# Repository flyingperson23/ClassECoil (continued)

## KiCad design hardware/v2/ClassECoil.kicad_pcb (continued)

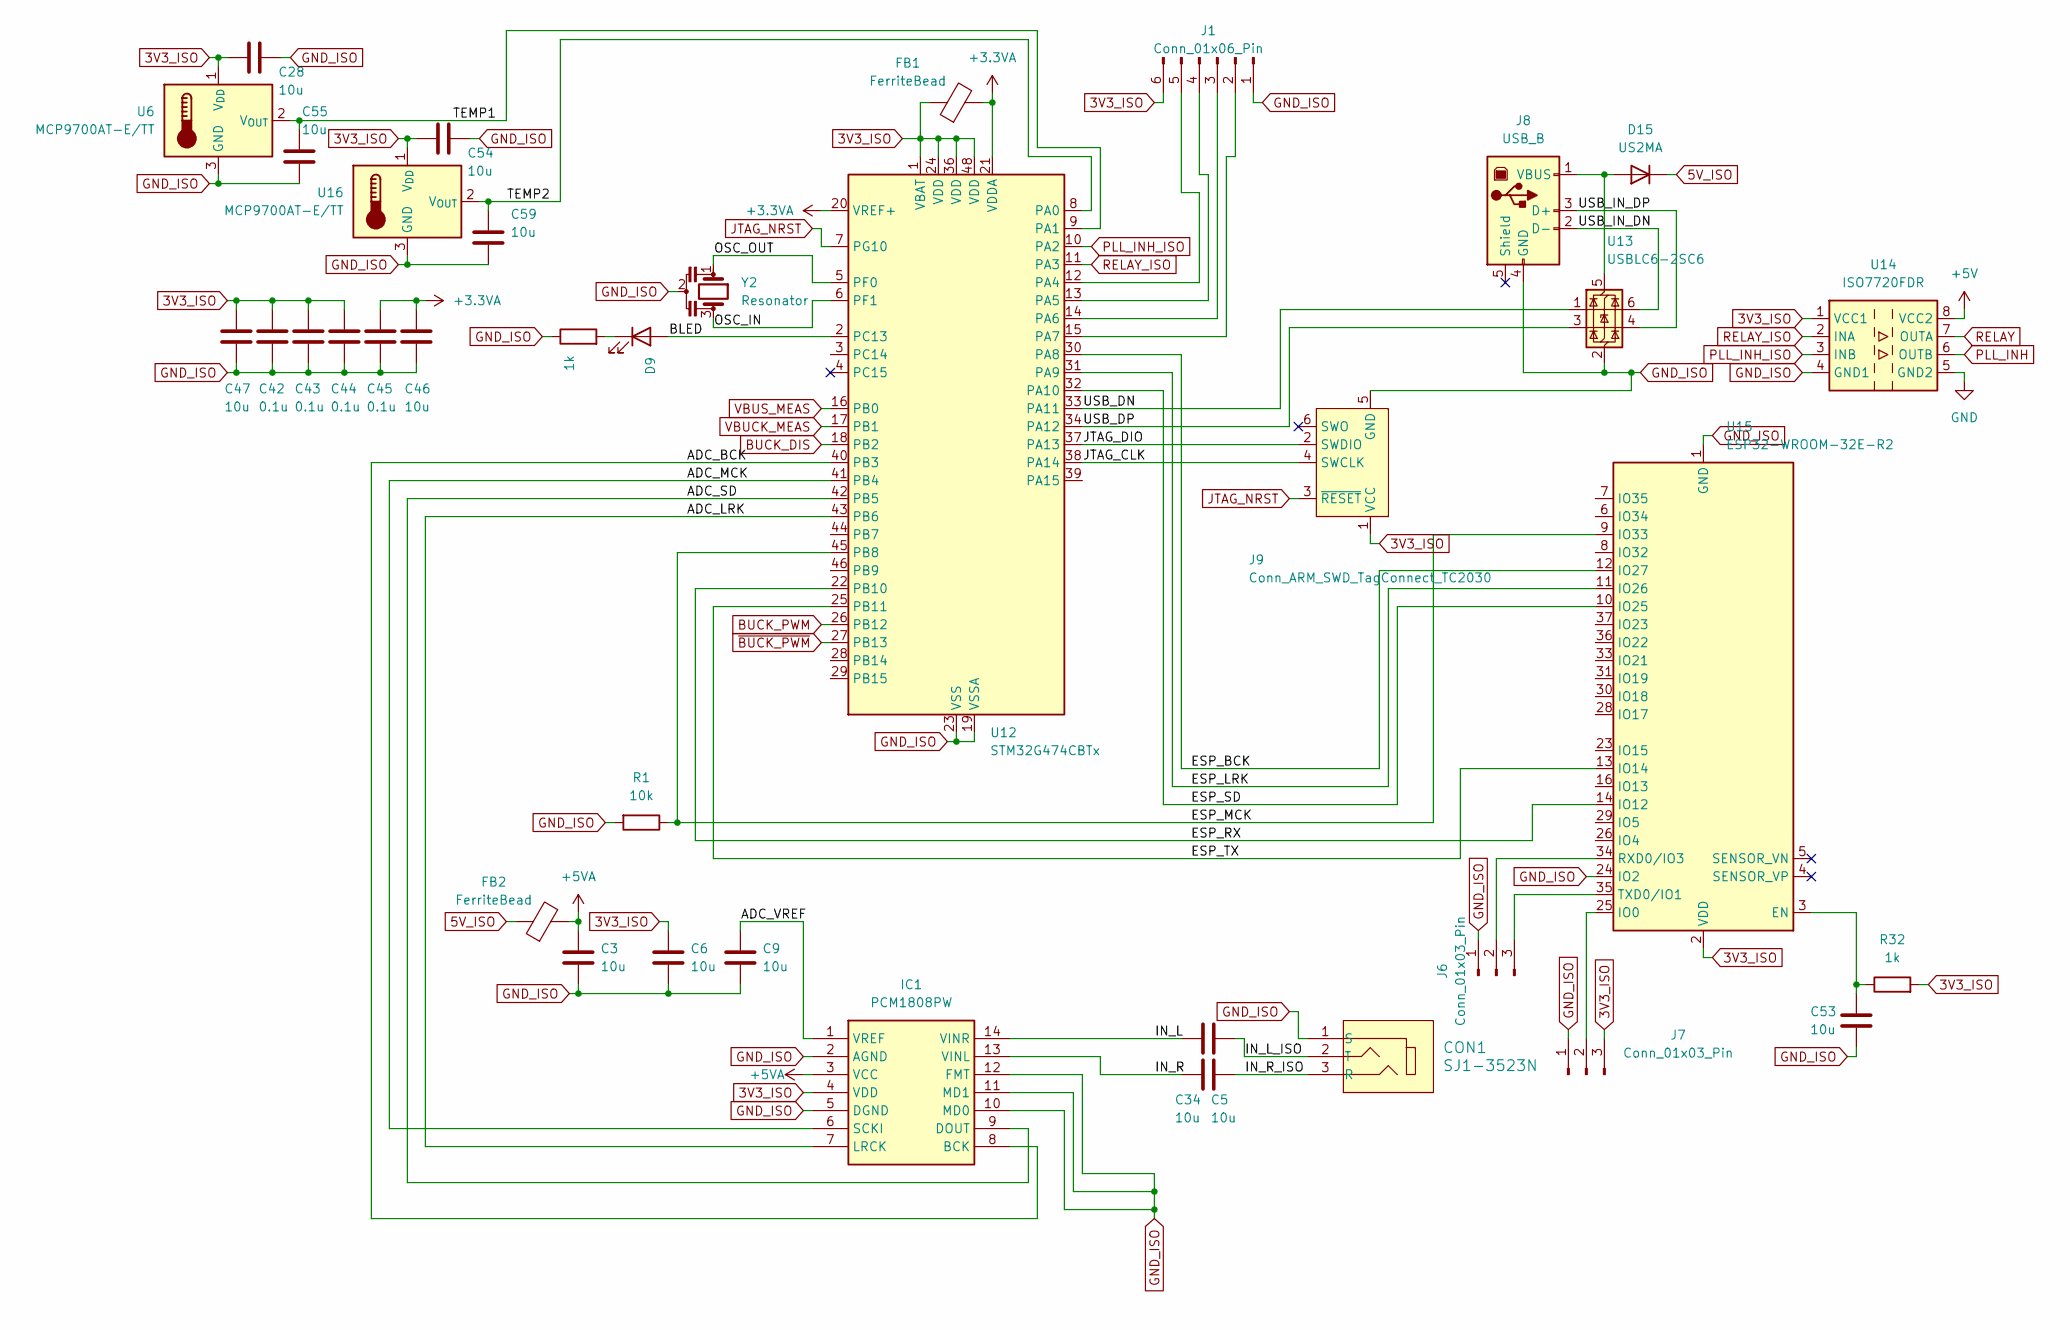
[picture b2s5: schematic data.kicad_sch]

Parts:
C3, C5, C6, C9, C28, C34, C46, C47, C53, C54, C55, C59: 10u; C_0805_2012Metric
C42, C43, C44, C45: 0.1u; C_0805_2012Metric
CON1: SJ1-3523N; Headphone_Jack_3.5mm_SJ1-3523N; MPN SJ1-3523N; Digi-Key_PN CP1-3523N-ND
D9: LED; LED_0805_2012Metric
D15: US2MA; D_SMA
FB1, FB2: FerriteBead; L_0805_2012Metric
IC1: PCM1808PW; TSSOP-14_4.4x5mm_P0.65mm; Mouser Part Number 595-PCM1808PW
J1: Conn_01x06_Pin; Molex_KK-254_AE-6410-06A_1x06_P2.54mm_Vertical
J6, J7: Conn_01x03_Pin; PinHeader_1x03_P2.54mm_Vertical
J8: USB_B; USB_B_OST_USB-B1HSxx_Horizontal
J9: Conn_ARM_SWD_TagConnect_TC2030; Tag-Connect_TC2030-IDC-FP_2x03_P1.27mm_Vertical
R1: 10k; R_0805_2012Metric
R10, R32: 1k; R_0805_2012Metric
U6, U16: MCP9700AT-E/TT; SOT-23
U12: STM32G474CBTx; LQFP-48_7x7mm_P0.5mm
U13: USBLC6-2SC6; SOT-23-6
U14: ISO7720FDR; SOIC-8_3.9x4.9mm_P1.27mm
U15: ESP32-WROOM-32E-R2; ESP32-WROOM-32D
Y2: Resonator; Resonator_SMD_Murata_CSTxExxV-3Pin_3.0x1.1mm

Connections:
3V3_ISO: C6.2, C28.2, C42.1, C43.1, C44.1, C47.2, C54.2, FB1.1, IC1.4 (VDD), J1.6, J7.3, J9.1 (VCC), R32.2, U6.1 (V_{DD}), U12.1 (VBAT), U12.24 (VDD), U12.36 (VDD), U12.48 (VDD), U14.1 (VCC1), U15.2 (VDD), U16.1 (V_{DD}); also elsewhere on the board
5V_ISO: D15.1 (K), FB2.1; also elsewhere on the board
+3.3VA: C45.1, C46.2, FB1.2, U12.20 (VREF+), U12.21 (VDDA)
+5V: U14.8 (VCC2); also elsewhere on the board
+5VA: C3.2, FB2.2, IC1.3 (VCC)
/Data Processing/ADC_BCK: IC1.8 (BCK), U12.40 (PB3)
/Data Processing/ADC_LRK: IC1.7 (LRCK), U12.43 (PB6)
/Data Processing/ADC_MCK: IC1.6 (SCKI), U12.41 (PB4)
/Data Processing/ADC_SD: IC1.9 (DOUT), U12.42 (PB5)
/Data Processing/ADC_VREF: C9.2, IC1.1 (VREF)
/Data Processing/BLED: D9.2 (A), U12.2 (PC13)
/Data Processing/ESP_BCK: U12.30 (PA8), U15.12 (IO27)
/Data Processing/ESP_LRK: U12.31 (PA9), U15.11 (IO26)
/Data Processing/ESP_MCK: R1.1, U12.45 (PB8), U15.9 (IO33)
/Data Processing/ESP_RX: U12.22 (PB10), U15.14 (IO12)
/Data Processing/ESP_SD: U12.32 (PA10), U15.10 (IO25)
/Data Processing/ESP_TX: U12.25 (PB11), U15.13 (IO14)
/Data Processing/IN_L: C5.1, IC1.14 (VINR)
/Data Processing/IN_L_ISO: C5.2, CON1.2 (T)
/Data Processing/IN_R: C34.1, IC1.13 (VINL)
/Data Processing/IN_R_ISO: C34.2, CON1.3 (R)
/Data Processing/JTAG_CLK: J9.4 (SWCLK), U12.38 (PA14)
/Data Processing/JTAG_DIO: J9.2 (SWDIO), U12.37 (PA13)
/Data Processing/OSC_IN: U12.6 (PF1), Y2.3
/Data Processing/OSC_OUT: U12.5 (PF0), Y2.1
/Data Processing/TEMP1: C55.1, U6.2 (V_{OUT}), U12.9 (PA1)
/Data Processing/TEMP2: C59.1, U12.8 (PA0), U16.2 (V_{OUT})
/Data Processing/USB_DN: U12.33 (PA11), U13.1 (I/O1)
/Data Processing/USB_DP: U12.34 (PA12), U13.3 (I/O2)
/Data Processing/USB_IN_DN: J8.2 (D-), U13.6 (I/O1)
/Data Processing/USB_IN_DP: J8.3 (D+), U13.4 (I/O2)
BUCK_DIS: U12.18 (PB2); also elsewhere on the board
BUCK_PWM: U12.26 (PB12); also elsewhere on the board
GND: U14.5 (GND2); also elsewhere on the board
GND_ISO: C3.1, C6.1, C9.1, C28.1, C42.2, C43.2, C44.2, C45.2, C46.1, C47.1, C53.1, C54.1, C55.2, C59.2, CON1.1 (S), IC1.2 (AGND), IC1.5 (DGND), IC1.10 (MD0), IC1.11 (MD1), IC1.12 (FMT), J1.1, J6.1, J7.1, J8.4 (GND), J9.5 (GND), R1.2, R10.1, U6.3 (GND), U12.19 (VSSA), U12.23 (VSS), U12.35 (VSS), U12.47 (VSS), U13.2 (GND), U14.4 (GND1), U15.1 (GND), U15.15 (GND), U15.24 (IO2), U15.38 (GND), U15.39 (GND), U16.3 (GND), Y2.2; also elsewhere on the board
JTAG_NRST: J9.3 (~RESET), U12.7 (PG10)
unnamed: D9.1 (K), R10.2
unnamed: D15.2 (A), J8.1 (VBUS), U13.5 (VBUS)
unnamed: J1.2, U12.15 (PA7)
unnamed: J1.3, U12.14 (PA6)
unnamed: J1.4, U12.13 (PA5)
unnamed: J1.5, U12.12 (PA4)
unnamed: J6.2, U15.34 (RXD0/IO3)
unnamed: J6.3, U15.35 (TXD0/IO1)
unnamed: J7.2, U15.25 (IO0)
unnamed: C53.2, R32.1, U15.3 (EN)
PLL_INH: U14.6 (OUTB); also elsewhere on the board
PLL_INH_ISO: U12.10 (PA2), U14.3 (INB)
RELAY: U14.7 (OUTA); also elsewhere on the board
RELAY_ISO: U12.11 (PA3), U14.2 (INA)
VBUCK_MEAS: U12.17 (PB1); also elsewhere on the board
VBUS_MEAS: U12.16 (PB0); also elsewhere on the board
~BUCK_PWM: U12.27 (PB13); also elsewhere on the board

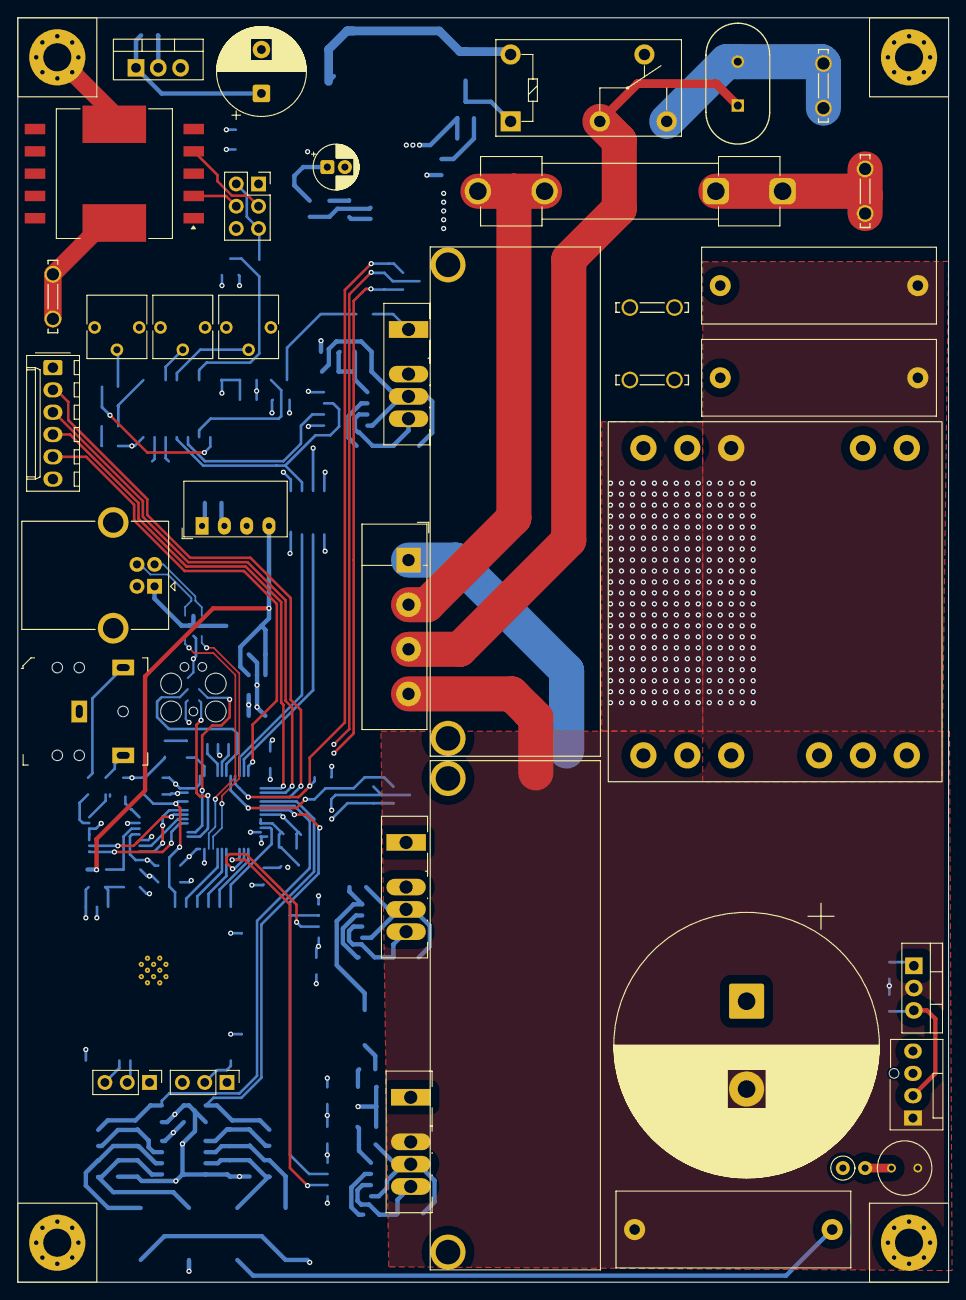
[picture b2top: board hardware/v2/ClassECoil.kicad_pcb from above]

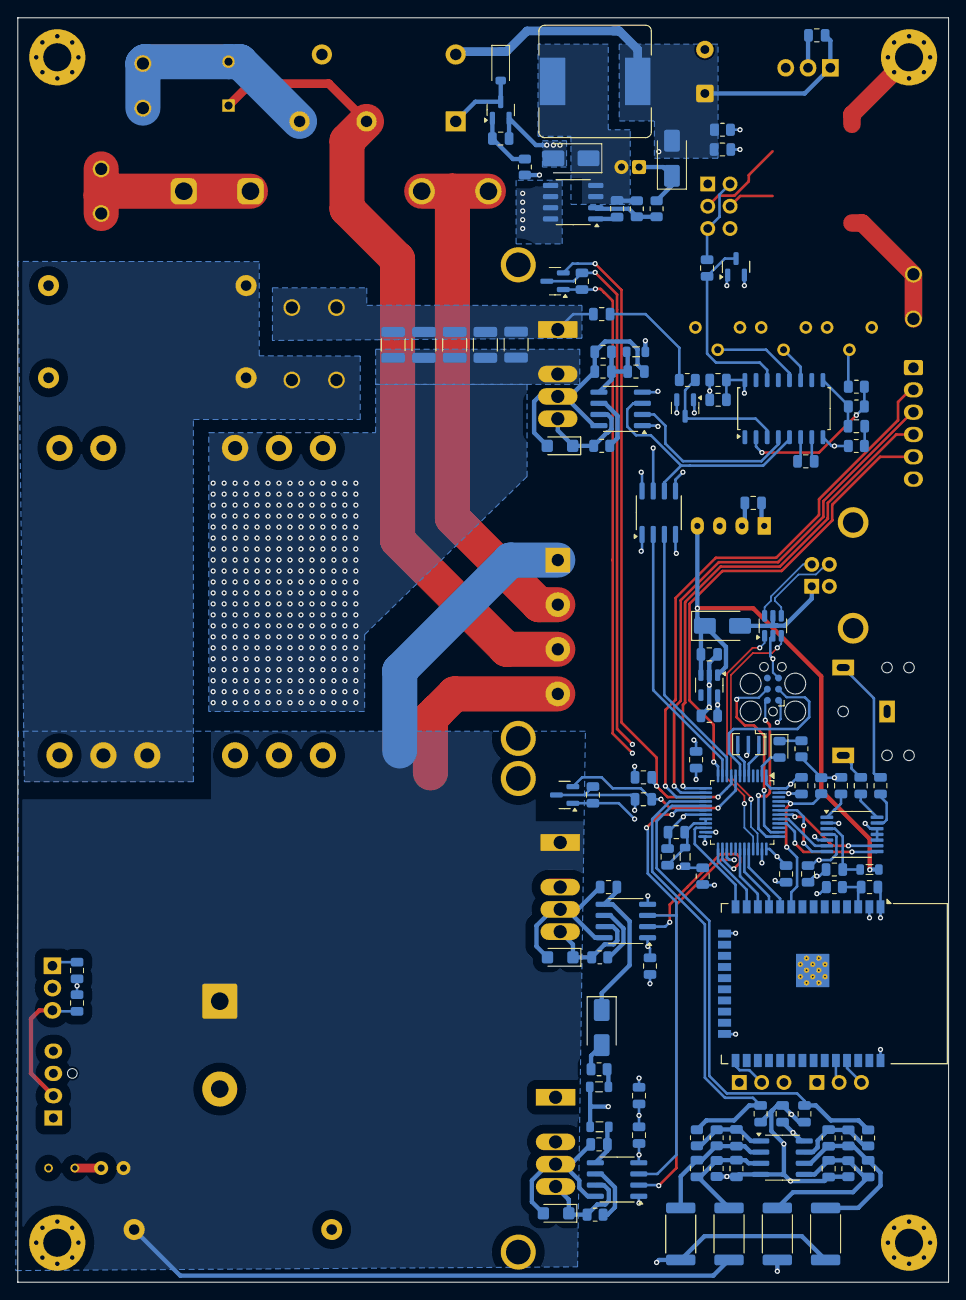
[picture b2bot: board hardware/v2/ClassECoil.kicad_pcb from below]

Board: 4 copper layers, 106.0 x 144.0 mm, 153 parts (112 on the bottom side), 107 nets.

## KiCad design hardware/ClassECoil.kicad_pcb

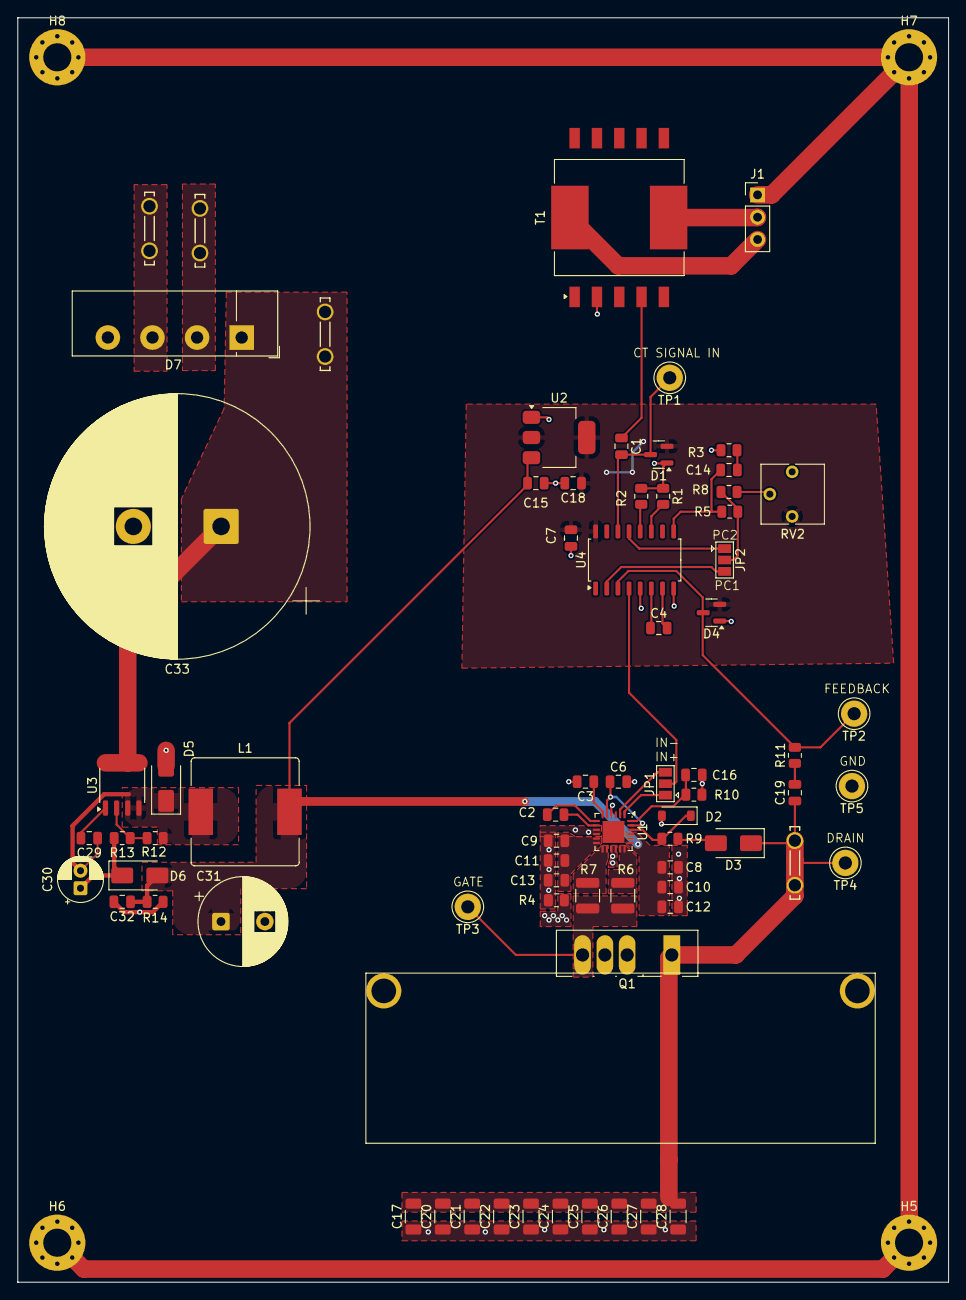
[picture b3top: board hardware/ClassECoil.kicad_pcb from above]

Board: 2 copper layers, 106.0 x 144.0 mm, 78 parts (0 on the bottom side), 43 nets.

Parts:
C1: 10n; C_0805_2012Metric
C2: 470n; C_0805_2012Metric
C3, C6, C7, C8, C9, C10, C11, C15, C18: 2.2u; C_0805_2012Metric
C4: 100p; C_0805_2012Metric
C12, C13, C16: 100n; C_0805_2012Metric
C14, C19: 1n; C_0805_2012Metric
C17, C20, C21, C22, C23, C24, C25, C26, C27, C28: 300p; C_1206_3216Metric
C29, C32: 0.1u; C_0805_2012Metric
C30: 860010572002; CP_Radial_D5.0mm_P2.00mm
C31: 860240475009; CP_Radial_D10.0mm_P5.00mm
C33: 861141085015; CP_Radial_D30.0mm_P10.00mm_SnapIn
D1, D4: BAV99; SOT-23
D2: MBR0540; D_SOD-123
D3: US1M; D_SMA
D5, D6: US2MA; D_SMA
D7: KBU8J; Diode_Bridge_Vishay_KBU
H5, H6, H7, H8: MountingHole_Pad; MountingHole_3.2mm_M3_Pad_Via
HS1: Heatsink_Pad; C40_Half
J1: Conn_01x03_Pin; PinHeader_1x03_P2.54mm_Vertical
J2, J3, J4, J5: Conn_01x01; SPADE_726386-2
JP1, JP2: SolderJumper_3_Open; SolderJumper-3_P1.3mm_Open_Pad1.0x1.5mm
L1: SRR1210A-821M; L_Bourns_SRR1210A
Q1: C3M0030090K; TO-247-4_Vertical
R1: 8.2k; R_0805_2012Metric
R2: 12k; R_0805_2012Metric
R3: 100R; R_0805_2012Metric
R4: 0R; R_0805_2012Metric
R5, R8: 60k; R_0805_2012Metric
R6, R7: 10R; R_1210_3225Metric
R9: 5.1k; R_0805_2012Metric
R10: 100k; R_0805_2012Metric
R11: 330k; R_0805_2012Metric
R12, R14: 10k; R_0805_2012Metric
R13: 62k; R_0805_2012Metric
RV2: T73YP103KT20; Potentiometer_Vishay_T73YP_Vertical
T1: CST2010-030LD; Transformer_Coilcraft_CST2010
TP1, TP2, TP3, TP4, TP5: TestPoint; Pin_D1.3mm_L11.0mm_LooseFit
U1: NCV51705MNTWG; QFN-24-1EP_4x4mm_P0.5mm_EP2.5x2.5mm
U2: NCP1117-5.0_SOT223; SOT-223-3_TabPin2
U3: AP3928S-13; SO-8_3.9x4.9mm_P1.27mm
U4: CD74HCT4046AM1; SOIC-16_4.55x10.3mm_P1.27mm

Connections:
+5V: C7.1, C18.1, D1.2 (A), D4.2 (A), RV2.3, U2.2 (VO), U4.16 (VDD)
BUCK_FB: R12.1, R13.1, U3.2 (FB)
Earth: H5.1, H6.1, H7.1, H8.1, J1.1
FEEDBACK: D4.3 (K), R11.2, TP2.1, U4.3 (RefIn)
GND: C3.2, C6.2, C7.2, C15.2, C16.1, C17.1, C18.2, C20.1, C21.1, C22.1, C23.1, C24.1, C25.1, C26.1, C27.1, C28.1, C31.2, C32.2, C33.2, D1.1 (K), D4.1 (K), D5.2 (A), D7.4 (-), Q1.2 (S), R1.1, R2.1, R3.2, R4.1, R10.1, R14.2, RV2.1, T1.2, TP5.1, U1.4 (SGND), U2.1 (GND), U4.5 (Inh), U4.8 (VSS)
unnamed: C1.1, T1.4
unnamed: C14.2, R3.1
unnamed: C19.2, R11.1
unnamed: D2.1 (K), R9.2, U1.22 (DESAT)
unnamed: D3.2 (A), R9.1
unnamed: C17.2, C19.1, C20.2, C21.2, C22.2, C23.2, C24.2, C25.2, C26.2, C27.2, C28.2, D3.1 (K), J3.1, Q1.1 (D), TP4.1
unnamed: C29.1, C30.2, D5.1 (K), L1.1, R12.2, U3.3 (GNDA), U3.4 (GNDP)
unnamed: C30.1, D6.1 (K), R13.2
unnamed: J1.2, T1.12
unnamed: J1.3, T1.11
unnamed: D7.3, J4.1
unnamed: D7.2, J5.1
unnamed: JP1.1 (A), U1.1 (IN+)
unnamed: JP1.3 (B), U1.2 (IN-)
unnamed: JP1.2 (C), U4.4 (FOUT)
unnamed: JP2.1 (A), U4.13 (PC2)
unnamed: JP2.3 (B), U4.2 (PC1)
unnamed: JP2.2 (C), R5.2, R8.1
unnamed: Q1.4 (G), R6.2, R7.2, TP3.1
unnamed: R6.1, U1.17 (OUTSRC), U1.18 (OUTSRC)
unnamed: R7.1, U1.13 (OUTSNK), U1.14 (OUTSNK)
unnamed: R8.2, RV2.2
unnamed: C2.1, U1.7 (C+)
unnamed: C2.2, U1.8 (C-)
unnamed: C16.2, R10.2, U1.24 (UVSET)
unnamed: C29.2, U3.1 (VCC)
unnamed: C4.1, U4.6 (C1)
unnamed: C4.2, U4.7 (C2)
unnamed: R1.2, U4.11 (R1)
unnamed: R2.2, U4.12 (R2)
unnamed: C1.2, D1.3 (K), TP1.1, U4.14 (SigIn)
unnamed: C14.1, R5.1, U4.9 (VCOin)
PGND: C8.2, C9.1, C10.2, C11.1, C12.2, C13.1, D2.2 (A), Q1.3 (DS), R4.2, U1.9 (PGND), U1.10 (PGND), U1.15 (PGND), U1.16 (PGND)
V5V: C6.1, U1.5 (VEESET), U1.23 (V5V)
VBUS: C33.1, D7.1 (+), J2.1, U3.5 (DRAIN), U3.6 (DRAIN), U3.7 (DRAIN), U3.8 (DRAIN)
VCH: C3.1, U1.6 (VCH)
VDD: C8.1, C10.1, C12.1, C15.1, C31.1, C32.1, D6.2 (A), L1.2, R14.1, U1.19 (VDD), U1.20 (VDD), U1.21 (SVDD), U2.3 (VI)
VEE: C9.2, C11.2, C13.2, U1.11 (VEE), U1.12 (VEE)

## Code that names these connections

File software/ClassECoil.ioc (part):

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Mcu.Name=STM32G474C(B-C-E)Tx
Mcu.Package=LQFP48
Mcu.UserName=STM32G474CBTx
PA0.Mode=IN1-Single-Ended
PA0.Signal=ADC2_IN1
PA1.Mode=IN2-Single-Ended
PA1.Signal=ADC2_IN2
PA10.Mode=SAI_A_MasterWithClock
PA10.Signal=SAI1_SD_A
PA11.Mode=Device
PA11.Signal=USB_DM
PA12.Mode=Device
PA12.Signal=USB_DP
PA13.Mode=Serial_Wire
PA13.Signal=SYS_JTMS-SWDIO
PA14.Mode=Serial_Wire
PA14.Signal=SYS_JTCK-SWCLK
PA2.GPIOParameters=GPIO_Label
PA2.GPIO_Label=PLL_INH
PA2.Signal=GPIO_Output
PA3.GPIOParameters=GPIO_Label
PA3.GPIO_Label=RELAY
PA3.Signal=GPIO_Output
PA4.Mode=IN17-Single-Ended
PA4.Signal=ADC2_IN17
PA5.Mode=IN13-Single-Ended
PA5.Signal=ADC2_IN13
PA6.Mode=IN3-Single-Ended
PA6.Signal=ADC2_IN3
PA7.Mode=IN4-Single-Ended
PA7.Signal=ADC2_IN4
PA8.Mode=SAI_A_MasterWithClock
PA8.Signal=SAI1_SCK_A
PA9.Mode=SAI_A_MasterWithClock
PA9.Signal=SAI1_FS_A
PB0.GPIOParameters=GPIO_Label
PB0.GPIO_Label=VBUS
PB0.Mode=IN15-Single-Ended
PB0.Signal=ADC1_IN15
PB1.GPIOParameters=GPIO_Label
PB1.GPIO_Label=VBUCK
PB1.Signal=SharedAnalog_PB1
PB10.Mode=Asynchronous
PB10.Signal=USART3_TX
PB11.Mode=Asynchronous
PB11.Signal=USART3_RX
PB12.Mode=Output_TC1TC2
PB12.Signal=HRTIM1_CHC1
PB13.Mode=Output_TC1TC2
PB13.Signal=HRTIM1_CHC2
PB2.GPIOParameters=GPIO_Label
PB2.GPIO_Label=BUCK_DIS
PB2.Signal=GPIO_Output
PB3.Mode=SAI_B_MasterWithClock
PB3.Signal=SAI1_SCK_B
PB4.Mode=SAI_B_MasterWithClock
PB4.Signal=SAI1_MCLK_B
PB5.Mode=SAI_B_MasterWithClock
PB5.Signal=SAI1_SD_B
PB6.Mode=SAI_B_MasterWithClock
PB6.Signal=SAI1_FS_B
PB8-BOOT0.Mode=SAI_A_MasterWithClock
PB8-BOOT0.Signal=SAI1_MCLK_A
PC13.GPIOParameters=GPIO_Label
PC13.GPIO_Label=BLED
PC13.Signal=GPIO_Output
PF0-OSC_IN.Mode=HSE-External-Oscillator
PF0-OSC_IN.Signal=RCC_OSC_IN
PF1-OSC_OUT.Mode=HSE-External-Oscillator
PF1-OSC_OUT.Signal=RCC_OSC_OUT
RCC.HSE_VALUE=8000000
RCC.SYSCLKFreq_VALUE=170000000
RCC.SYSCLKSource=RCC_SYSCLKSOURCE_PLLCLK
board=custom

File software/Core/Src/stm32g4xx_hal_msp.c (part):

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
    __HAL_RCC_GPIOA_CLK_ENABLE();
    /**ADC1 GPIO Configuration
    PA2     ------> ADC1_IN3
    PA3     ------> ADC1_IN4
    */
    GPIO_InitStruct.Pin = VBUS_MEAS_Pin|VBUCK_MEAS_Pin;
    GPIO_InitStruct.Mode = GPIO_MODE_ANALOG;
    GPIO_InitStruct.Pull = GPIO_NOPULL;
    HAL_GPIO_Init(GPIOA, &GPIO_InitStruct);
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    __HAL_RCC_GPIOA_CLK_ENABLE();
    __HAL_RCC_GPIOB_CLK_ENABLE();
    /**ADC2 GPIO Configuration
    PA7     ------> ADC2_IN4
    PB2     ------> ADC2_IN12
    */
    GPIO_InitStruct.Pin = GPIO_PIN_7;
    GPIO_InitStruct.Mode = GPIO_MODE_ANALOG;
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
    __HAL_RCC_GPIOB_CLK_ENABLE();
    /**ADC3 GPIO Configuration
    PB0     ------> ADC3_IN12
    PB1     ------> ADC3_IN1
    */
    GPIO_InitStruct.Pin = GPIO_PIN_0|GPIO_PIN_1;
    GPIO_InitStruct.Mode = GPIO_MODE_ANALOG;
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    }

    /**ADC1 GPIO Configuration
    PA2     ------> ADC1_IN3
    PA3     ------> ADC1_IN4
    */
    HAL_GPIO_DeInit(GPIOA, VBUS_MEAS_Pin|VBUCK_MEAS_Pin);

    /* USER CODE BEGIN ADC1_MspDeInit 1 */

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    }

    /**ADC2 GPIO Configuration
    PA7     ------> ADC2_IN4
    PB2     ------> ADC2_IN12
    */
    HAL_GPIO_DeInit(GPIOA, GPIO_PIN_7);

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    }

    /**ADC3 GPIO Configuration
    PB0     ------> ADC3_IN12
    PB1     ------> ADC3_IN1
    */
    HAL_GPIO_DeInit(GPIOB, GPIO_PIN_0|GPIO_PIN_1);

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
    __HAL_RCC_GPIOA_CLK_ENABLE();
    /**COMP2 GPIO Configuration
    PA3     ------> COMP2_INP
    */
    GPIO_InitStruct.Pin = VBUCK_MEAS_Pin;
    GPIO_InitStruct.Mode = GPIO_MODE_ANALOG;
    GPIO_InitStruct.Pull = GPIO_NOPULL;
    HAL_GPIO_Init(VBUCK_MEAS_GPIO_Port, &GPIO_InitStruct);

    /* USER CODE BEGIN COMP2_MspInit 1 */

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    /* USER CODE END COMP2_MspDeInit 0 */

    /**COMP2 GPIO Configuration
    PA3     ------> COMP2_INP
    */
    HAL_GPIO_DeInit(VBUCK_MEAS_GPIO_Port, VBUCK_MEAS_Pin);

    /* USER CODE BEGIN COMP2_MspDeInit 1 */

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
    __HAL_RCC_GPIOB_CLK_ENABLE();
    /**HRTIM1 GPIO Configuration
    PB12     ------> HRTIM1_CHC1
    PB13     ------> HRTIM1_CHC2
    */
    GPIO_InitStruct.Pin = GPIO_PIN_12|GPIO_PIN_13;
    GPIO_InitStruct.Mode = GPIO_MODE_AF_PP;
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
    __HAL_RCC_GPIOA_CLK_ENABLE();
    /**TIM2 GPIO Configuration
    PA0     ------> TIM2_CH1
    */
    GPIO_InitStruct.Pin = PLL_INH_Pin;
    GPIO_InitStruct.Mode = GPIO_MODE_AF_PP;
    GPIO_InitStruct.Pull = GPIO_NOPULL;
    GPIO_InitStruct.Speed = GPIO_SPEED_FREQ_LOW;
    GPIO_InitStruct.Alternate = GPIO_AF1_TIM2;
    HAL_GPIO_Init(PLL_INH_GPIO_Port, &GPIO_InitStruct);

    /* USER CODE BEGIN TIM2_MspPostInit 1 */

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
    __HAL_RCC_GPIOB_CLK_ENABLE();
    /**USART3 GPIO Configuration
    PB10     ------> USART3_TX
    PB11     ------> USART3_RX
    */
    GPIO_InitStruct.Pin = GPIO_PIN_10|GPIO_PIN_11;
    GPIO_InitStruct.Mode = GPIO_MODE_AF_PP;
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    __HAL_RCC_USART3_CLK_DISABLE();

    /**USART3 GPIO Configuration
    PB10     ------> USART3_TX
    PB11     ------> USART3_RX
    */
    HAL_GPIO_DeInit(GPIOB, GPIO_PIN_10|GPIO_PIN_11);

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    SAI1_client ++;

    /**SAI1_A_Block_A GPIO Configuration
    PA8     ------> SAI1_SCK_A
    PA9     ------> SAI1_FS_A
    PA10     ------> SAI1_SD_A
    PB8-BOOT0     ------> SAI1_MCLK_A
    */
    GPIO_InitStruct.Pin = GPIO_PIN_8|GPIO_PIN_9|GPIO_PIN_10;
    GPIO_InitStruct.Mode = GPIO_MODE_AF_PP;
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    SAI1_client ++;

    /**SAI1_B_Block_B GPIO Configuration
    PB3     ------> SAI1_SCK_B
    PB4     ------> SAI1_MCLK_B
    PB5     ------> SAI1_SD_B
    PB6     ------> SAI1_FS_B
    */
    GPIO_InitStruct.Pin = GPIO_PIN_3|GPIO_PIN_4|GPIO_PIN_6;
    GPIO_InitStruct.Mode = GPIO_MODE_AF_PP;
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      }

    /**SAI1_A_Block_A GPIO Configuration
    PA8     ------> SAI1_SCK_A
    PA9     ------> SAI1_FS_A
    PA10     ------> SAI1_SD_A
    PB8-BOOT0     ------> SAI1_MCLK_A
    */
    HAL_GPIO_DeInit(GPIOA, GPIO_PIN_8|GPIO_PIN_9|GPIO_PIN_10);

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      }

    /**SAI1_B_Block_B GPIO Configuration
    PB3     ------> SAI1_SCK_B
    PB4     ------> SAI1_MCLK_B
    PB5     ------> SAI1_SD_B
    PB6     ------> SAI1_FS_B
    */
    HAL_GPIO_DeInit(GPIOB, GPIO_PIN_3|GPIO_PIN_4|GPIO_PIN_5|GPIO_PIN_6);

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
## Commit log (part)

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2025-11-16 v1 done?
2026-03-07 V3 build + order
